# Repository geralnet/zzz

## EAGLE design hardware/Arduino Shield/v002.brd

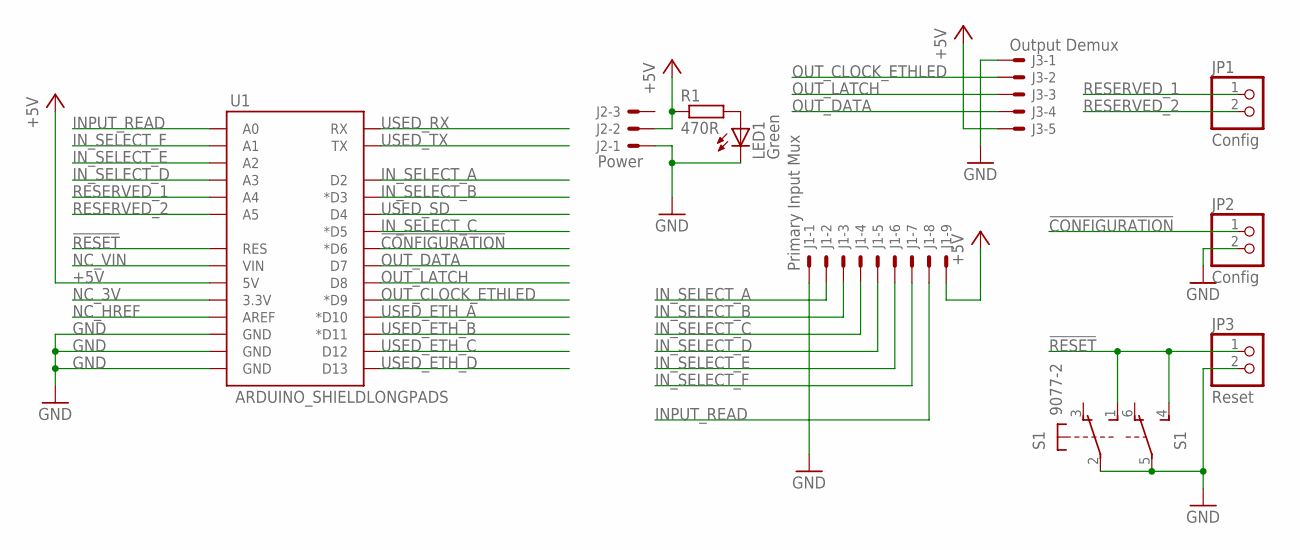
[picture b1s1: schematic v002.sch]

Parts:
J1: Primary Input Mux; 6410-09
J2: Power; 6410-03
J3: Output Demux; 6410-05
JP1, JP2: Config; 1X02
JP3: Reset; 1X02
LED1: Green; LED3MM
R1: 470R; 0204/7
S1: 9077-2
U1: ARDUINO_SHIELDLONGPADS; DUEMILANOVE_SHIELD_LONGPADS

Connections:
!CONFIGURATION: JP2.1, U1.D6 (*D6)
!RESET: JP3.1, S1.1 (S), S1.4 (S), U1.RES
+5V: J1.9, J2.2, J3.5, R1.1, U1.5V
GND: J1.1, J2.1, J3.1, JP2.2, JP3.2, LED1.K (C), S1.2, S1.5, U1.GND@0 (GND), U1.GND@1 (GND), U1.GND@2 (GND)
INPUT_READ: J1.8, U1.A0
IN_SELECT_A: J1.2, U1.D2
IN_SELECT_B: J1.3, U1.D3 (*D3)
IN_SELECT_C: J1.4, U1.D5 (*D5)
IN_SELECT_D: J1.5, U1.A3
IN_SELECT_E: J1.6, U1.A2
IN_SELECT_F: J1.7, U1.A1
unnamed: LED1.A, R1.2
NC_3V: U1.3.3V
NC_HREF: U1.AREF
NC_VIN: U1.VIN
OUT_CLOCK_ETHLED: J3.2, U1.D9 (*D9)
OUT_DATA: J3.4, U1.D7
OUT_LATCH: J3.3, U1.D8
RESERVED_1: JP1.1, U1.A4
RESERVED_2: JP1.2, U1.A5
USED_ETH_A: U1.D10 (*D10)
USED_ETH_B: U1.D11 (*D11)
USED_ETH_C: U1.D12
USED_ETH_D: U1.D13
USED_RX: U1.RX
USED_SD: U1.D4
USED_TX: U1.TX

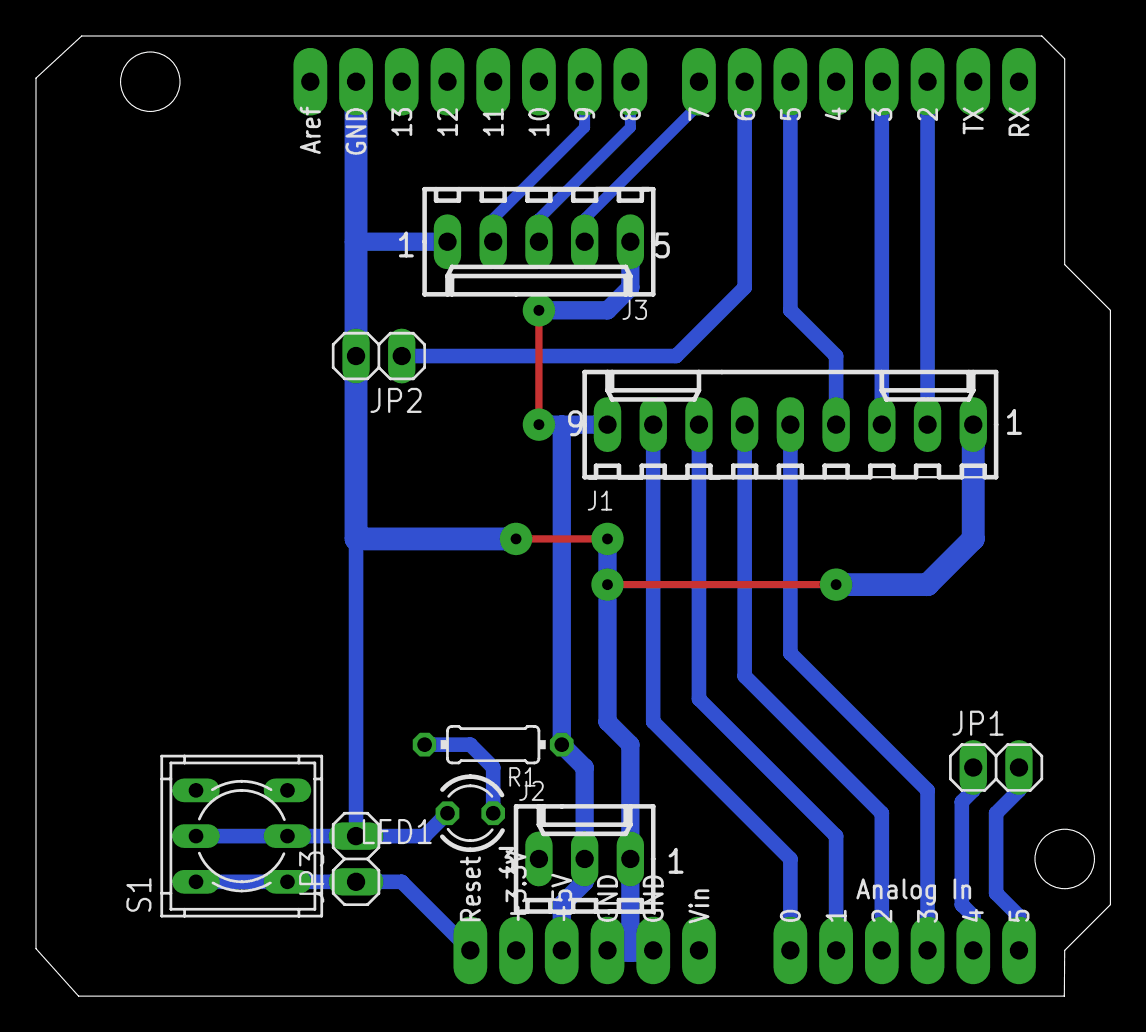
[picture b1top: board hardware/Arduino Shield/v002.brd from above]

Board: 2 copper layers, 59.7 x 53.3 mm, 10 parts (0 on the bottom side), 17 nets.

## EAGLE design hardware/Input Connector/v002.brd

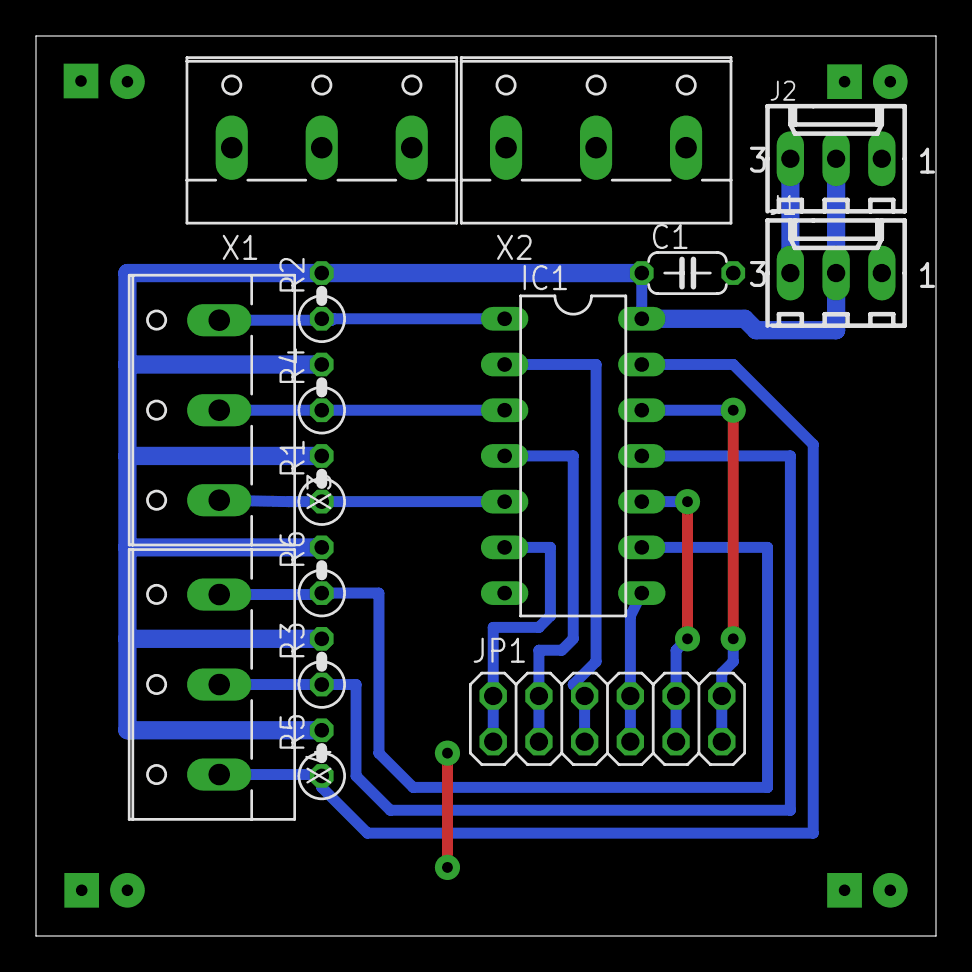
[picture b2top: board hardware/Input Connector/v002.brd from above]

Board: 2 copper layers, 50.0 x 50.0 mm, 16 parts (0 on the bottom side), 15 nets.

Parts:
C1: 0.1uF; C050-024X044
IC1: 7404; DIL14
J1: Pwr-1; 6410-03
J2: Pwr-2; 6410-03
JP1: Output; 2X06
PCB1: ZZZ_MODULE05X05; ZZZ_MODULE_05X05
R1, R2, R3, R4, R5, R6: 10K; 0207/2V
X1, X2: GND; W237-103
X3, X4: W237-103

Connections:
+5V: C1.1, IC1.14, J1.2, J2.2, R1.2, R2.2, R3.2, R4.2, R5.2, R6.2
+12V: J1.3, J2.3
GND: C1.2, IC1.7, J1.1, J2.1, PCB1.GND@1, PCB1.GND@2, PCB1.GND@3, PCB1.GND@4, PCB1.GND@5, PCB1.GND@6, PCB1.GND@7, PCB1.GND@8, X1.1, X1.2, X1.3, X2.1, X2.2, X2.3
unnamed: IC1.2, JP1.5, JP1.6
unnamed: IC1.1, R2.1, X3.3
unnamed: IC1.6, JP1.1, JP1.2
unnamed: IC1.5, R1.1, X3.1
unnamed: IC1.11, R3.1, X4.2
unnamed: IC1.10, JP1.9, JP1.10
unnamed: IC1.3, R4.1, X3.2
unnamed: IC1.12, JP1.11, JP1.12
unnamed: IC1.13, R5.1, X4.1
unnamed: IC1.8, JP1.7, JP1.8
unnamed: IC1.9, R6.1, X4.3
unnamed: IC1.4, JP1.3, JP1.4

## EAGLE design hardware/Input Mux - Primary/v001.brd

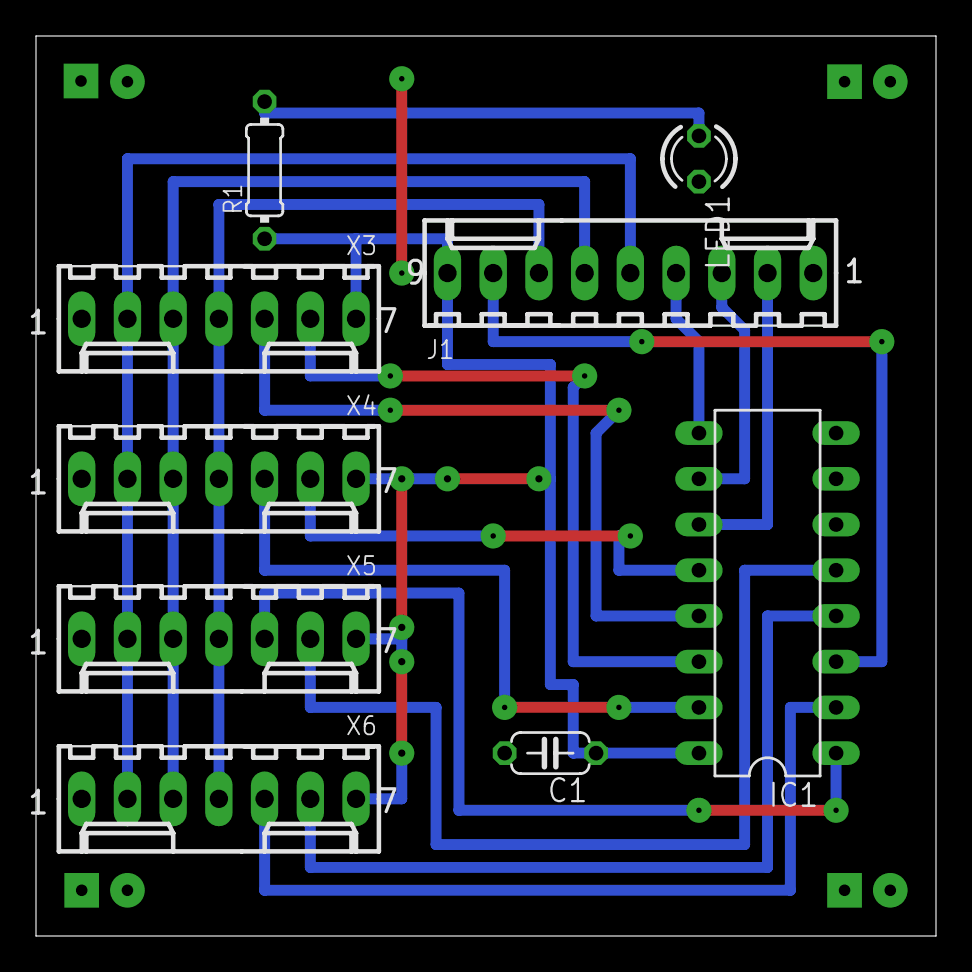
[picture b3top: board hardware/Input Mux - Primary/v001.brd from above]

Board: 2 copper layers, 50.0 x 50.0 mm, 10 parts (0 on the bottom side), 18 nets.

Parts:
C1: 0.1uF; C050-024X044
IC1: 4051N; DIL16
J1: To Arduino Shield; 6410-09
LED1: Green; LED3MM
PCB1: ZZZ_MODULE05X05; ZZZ_MODULE_05X05
R1: 470R; 0204/7
X3: Sec 12; 6410-07
X4: Sec 34; 6410-07
X5: Sec 56; 6410-07
X6: Sec 78; 6410-07

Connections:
+5V: C1.1, IC1.16, J1.9, R1.1, X3.7, X4.7, X5.7, X6.7
GND: C1.2, IC1.6, IC1.7, IC1.8, J1.1, LED1.K, PCB1.GND@1, PCB1.GND@2, PCB1.GND@3, PCB1.GND@4, PCB1.GND@5, PCB1.GND@6, PCB1.GND@7, PCB1.GND@8, X3.1, X4.1, X5.1, X6.1
INPUT_READ: IC1.3, J1.8
unnamed: LED1.A, R1.2
SECONDARY_1: IC1.13, X3.5
SECONDARY_2: IC1.14, X3.6
SECONDARY_3: IC1.15, X4.5
SECONDARY_4: IC1.12, X4.6
SECONDARY_5: IC1.1, X5.5
SECONDARY_6: IC1.5, X5.6
SECONDARY_7: IC1.2, X6.5
SECONDARY_8: IC1.4, X6.6
SELECT_A: IC1.11, J1.2
SELECT_B: IC1.10, J1.3
SELECT_C: IC1.9, J1.4
SELECT_D: J1.5, X3.2, X4.2, X5.2, X6.2
SELECT_E: J1.6, X3.3, X4.3, X5.3, X6.3
SELECT_F: J1.7, X3.4, X4.4, X5.4, X6.4

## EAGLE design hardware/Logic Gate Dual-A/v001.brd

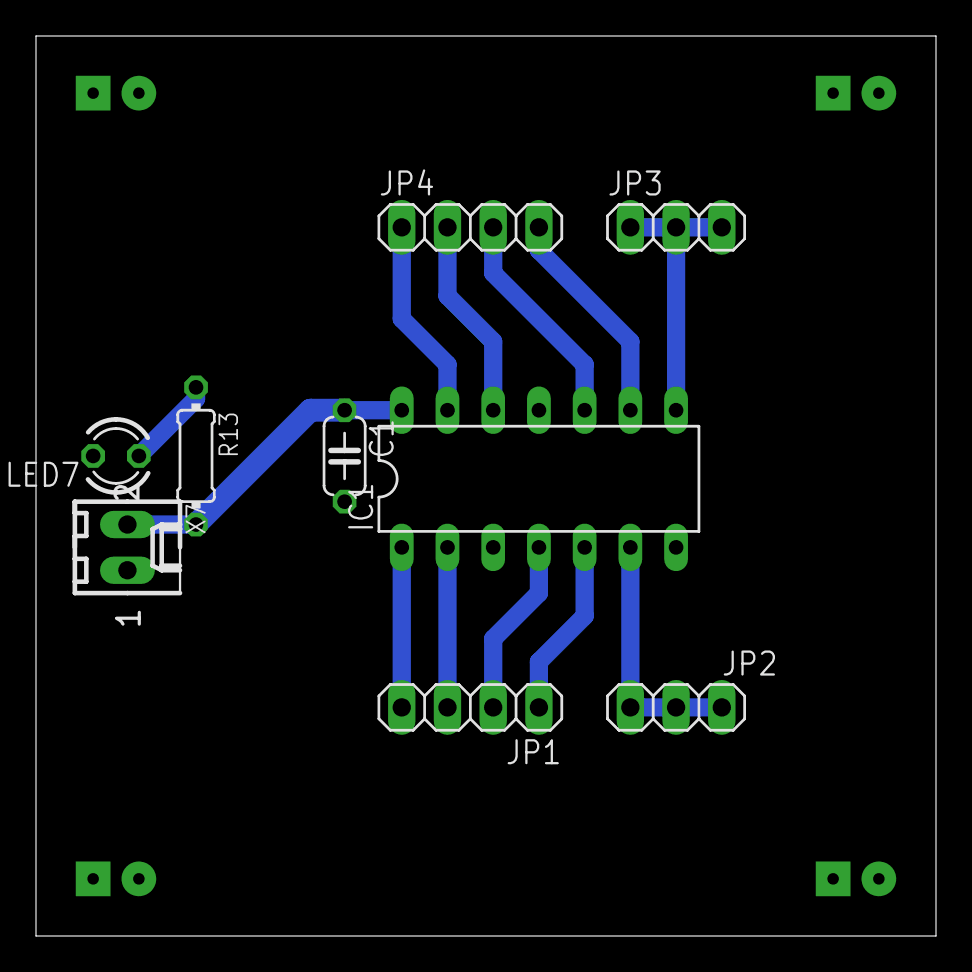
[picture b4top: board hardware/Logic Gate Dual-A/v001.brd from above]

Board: 2 copper layers, 50.0 x 50.0 mm, 10 parts (0 on the bottom side), 13 nets.

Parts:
C1: 0.1uF; C050-024X044
IC1: Like 7421; DIL14
JP1, JP4: Input; 1X04
JP2, JP3: Output; 1X03
LED7: Green; LED3MM
PCB1: PCB05X05; PCB_05X05
R13: 470R; 0204/7
X7: Power; 6410-02

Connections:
+5V: C1.1, IC1.14, R13.2, X7.2
GND: C1.2, IC1.7, LED7.K, PCB1.GND@1, PCB1.GND@2, PCB1.GND@3, PCB1.GND@4, PCB1.GND@5, PCB1.GND@6, PCB1.GND@7, PCB1.GND@8, X7.1
unnamed: IC1.1, JP1.4
unnamed: IC1.2, JP1.3
unnamed: IC1.6, JP2.1, JP2.2, JP2.3
unnamed: IC1.4, JP1.2
unnamed: LED7.A, R13.1
unnamed: IC1.5, JP1.1
unnamed: IC1.8, JP3.1, JP3.2, JP3.3
unnamed: IC1.9, JP4.4
unnamed: IC1.10, JP4.3
unnamed: IC1.12, JP4.2
unnamed: IC1.13, JP4.1

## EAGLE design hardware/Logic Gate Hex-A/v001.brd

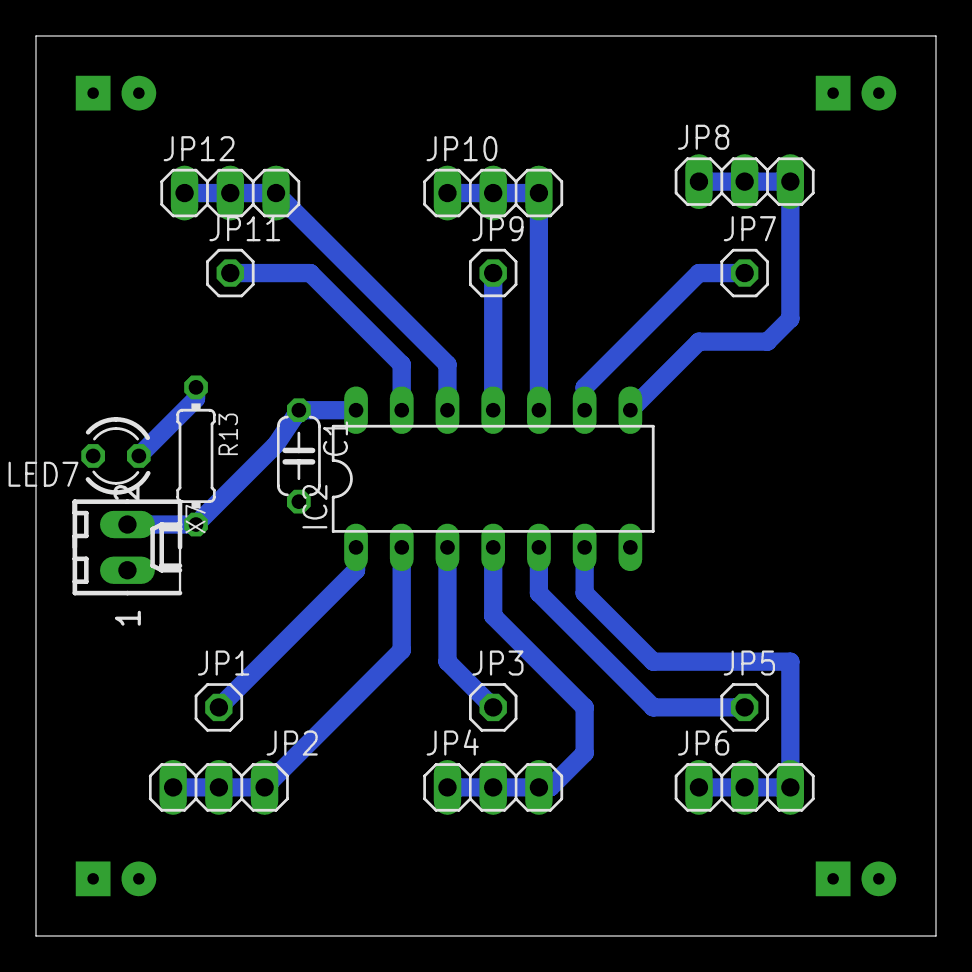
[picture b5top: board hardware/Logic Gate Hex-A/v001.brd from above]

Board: 2 copper layers, 50.0 x 50.0 mm, 18 parts (0 on the bottom side), 15 nets.

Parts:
C1: 0.1uF; C050-024X044
IC2: Like 7404; DIL14
JP1, JP3, JP5, JP7, JP9, JP11: 1X01
JP2, JP4, JP6, JP8, JP10, JP12: Output; 1X03
LED7: Green; LED3MM
PCB1: PCB05X05; PCB_05X05
R13: 470R; 0204/7
X7: Power; 6410-02

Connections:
+5V: C1.1, IC2.14, R13.2, X7.2
GND: C1.2, IC2.7, LED7.K, PCB1.GND@1, PCB1.GND@2, PCB1.GND@3, PCB1.GND@4, PCB1.GND@5, PCB1.GND@6, PCB1.GND@7, PCB1.GND@8, X7.1
JP12: IC2.12, JP12.1, JP12.2, JP12.3
unnamed: IC2.1, JP1.1
unnamed: IC2.2, JP2.1, JP2.2, JP2.3
unnamed: LED7.A, R13.1
unnamed: IC2.3, JP3.1
unnamed: IC2.4, JP4.1, JP4.2, JP4.3
unnamed: IC2.5, JP5.1
unnamed: IC2.6, JP6.1, JP6.2, JP6.3
unnamed: IC2.9, JP7.1
unnamed: IC2.8, JP8.1, JP8.2, JP8.3
unnamed: IC2.11, JP9.1
unnamed: IC2.10, JP10.1, JP10.2, JP10.3
unnamed: IC2.13, JP11.1

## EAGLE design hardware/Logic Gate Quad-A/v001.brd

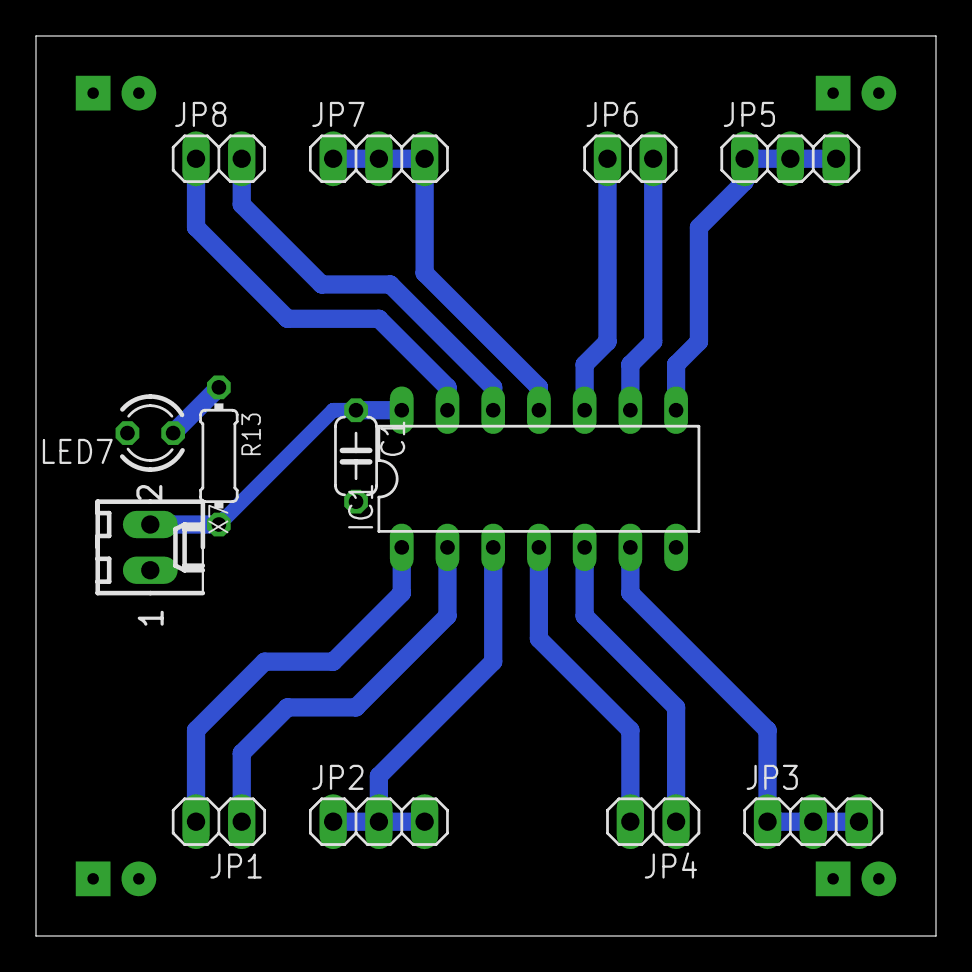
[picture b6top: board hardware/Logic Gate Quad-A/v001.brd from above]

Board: 2 copper layers, 50.0 x 50.0 mm, 14 parts (0 on the bottom side), 15 nets.

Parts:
C1: 0.1uF; C050-024X044
IC1: Like 7408; DIL14
JP1, JP4, JP6, JP8: 1X02
JP2, JP3, JP5, JP7: Output; 1X03
LED7: Green; LED3MM
PCB1: PCB05X05; PCB_05X05
R13: 470R; 0204/7
X7: Power; 6410-02

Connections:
+5V: C1.1, IC1.14, R13.2, X7.2
GND: C1.2, IC1.7, LED7.K, PCB1.GND@1, PCB1.GND@2, PCB1.GND@3, PCB1.GND@4, PCB1.GND@5, PCB1.GND@6, PCB1.GND@7, PCB1.GND@8, X7.1
unnamed: IC1.1, JP1.2
unnamed: IC1.2, JP1.1
unnamed: IC1.3, JP2.1, JP2.2, JP2.3
unnamed: IC1.4, JP4.2
unnamed: LED7.A, R13.1
unnamed: IC1.5, JP4.1
unnamed: IC1.6, JP3.1, JP3.2, JP3.3
unnamed: IC1.9, JP6.2
unnamed: IC1.10, JP6.1
unnamed: IC1.8, JP5.1, JP5.2, JP5.3
unnamed: IC1.12, JP8.2
unnamed: IC1.13, JP8.1
unnamed: IC1.11, JP7.1, JP7.2, JP7.3

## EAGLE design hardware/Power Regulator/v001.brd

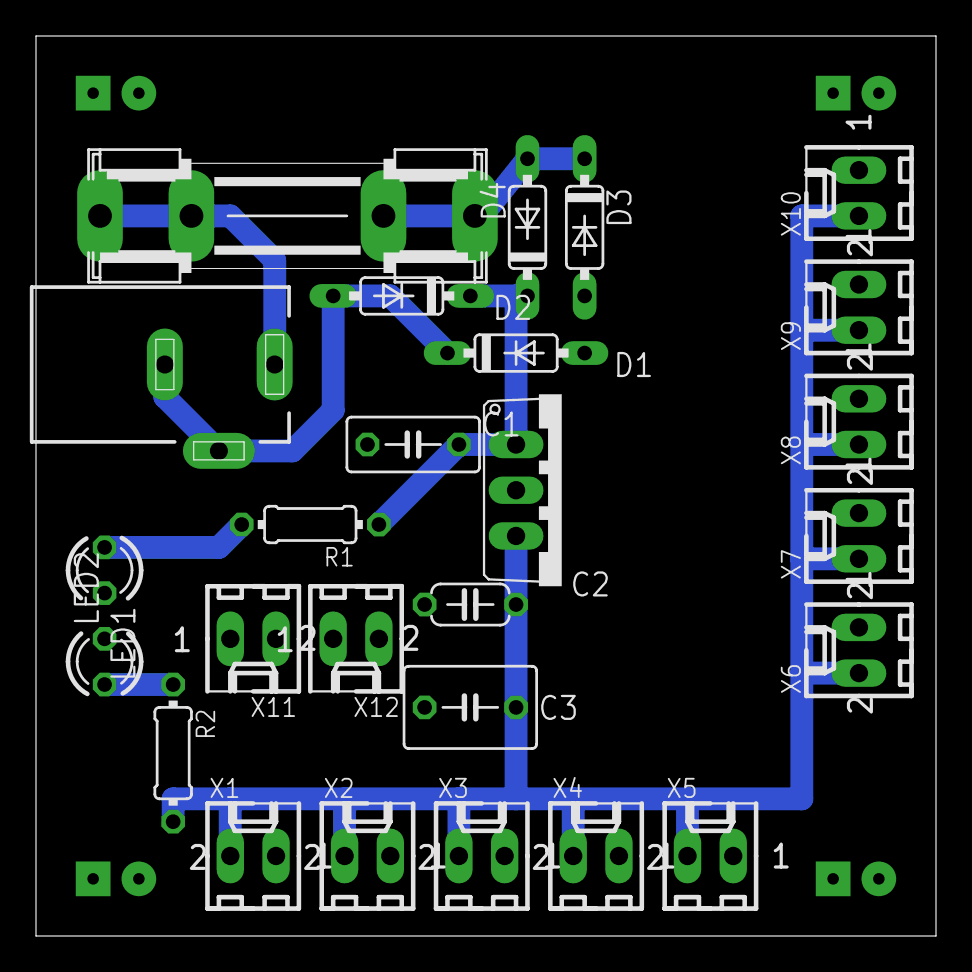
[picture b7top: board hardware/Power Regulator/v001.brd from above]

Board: 2 copper layers, 50.0 x 50.0 mm, 27 parts (0 on the bottom side), 8 nets.

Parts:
C1: 0.33uF; C050-030X075
C2: 0.1uF; C050-024X044
C3: 1uF; C050-045X075
D1, D2, D3, D4: 1N4004; DO35-7
F1: 1A; SHK20L
IC1: 7805TV; TO220V
J1: 9VDC; DCJ0202
LED1, LED2: GREEN; LED3MM
PCB1: PCB05X05; PCB_05X05
R1, R2: 470R; 0204/7
X1: Out-A; 6410-02
X2: Out-B; 6410-02
X3: Out-C; 6410-02
X4: Out-D; 6410-02
X5: Out-E; 6410-02
X6: Out-F; 6410-02
X7: Out-G; 6410-02
X8: Out-H; 6410-02
X9: Out-I; 6410-02
X10: Out-J; 6410-02
X11, X12: Cross; 6410-02

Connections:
+5V: C2.1, C3.1, IC1.3, R2.2, X1.2, X2.2, X3.2, X4.2, X5.2, X6.2, X7.2, X8.2, X9.2, X10.2
GND: C1.2, C2.2, C3.2, D1.A, D3.A, IC1.2, LED1.K, LED2.K, PCB1.GND@1, PCB1.GND@2, PCB1.GND@3, PCB1.GND@4, PCB1.GND@5, PCB1.GND@6, PCB1.GND@7, PCB1.GND@8, X1.1, X2.1, X3.1, X4.1, X5.1, X6.1, X7.1, X8.1, X9.1, X10.1, X11.1, X12.1
unnamed: C1.1, D2.C, D4.C, IC1.1, R1.1
unnamed: LED1.A, R1.2
unnamed: F1.1A, J1.1
unnamed: LED2.A, R2.1
unnamed: D1.C, D2.A, J1.2, J1.3
unnamed: D3.C, D4.A, F1.2A

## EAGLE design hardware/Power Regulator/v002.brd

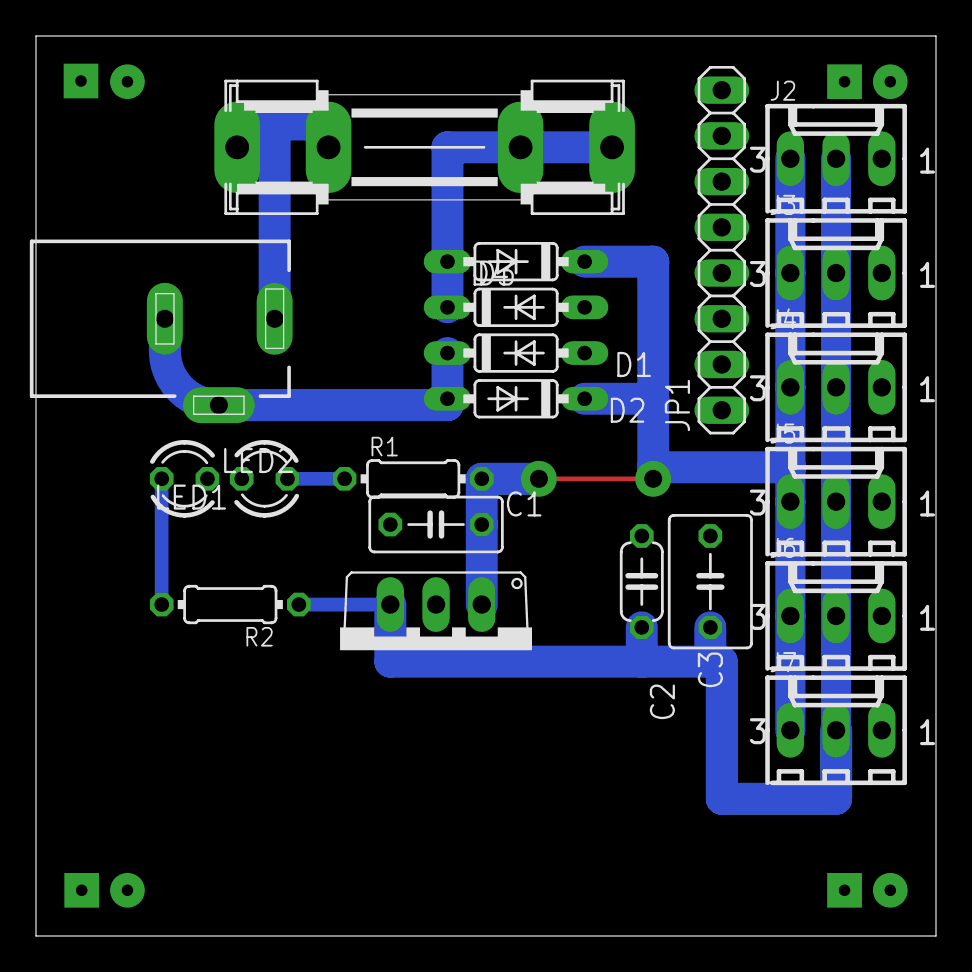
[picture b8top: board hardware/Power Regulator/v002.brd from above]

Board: 2 copper layers, 50.0 x 50.0 mm, 22 parts (0 on the bottom side), 8 nets.

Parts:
C1: 0.33uF; C050-030X075
C2: 0.1uF; C050-024X044
C3: 1uF; C050-045X075
D1, D2, D3, D4: 1N4004; DO35-7
F1: 3A; SHK20L
IC1: 7805TV; TO220V
J1: 12VDC; DCJ0202
J2: Out-1; 6410-03
J3: Out-2; 6410-03
J4: Out-3; 6410-03
J5: Out-4; 6410-03
J6: Out-5; 6410-03
J7: Out-6; 6410-03
JP1: GND; 1X08
LED1, LED2: GREEN; LED3MM
PCB1: ZZZ_MODULE05X05; ZZZ_MODULE_05X05
R1, R2: 470R; 0204/7

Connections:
+5V: C2.1, C3.1, IC1.3, J2.2, J3.2, J4.2, J5.2, J6.2, J7.2, R2.1
+12V: C1.1, D2.C, D4.C, IC1.1, J2.3, J3.3, J4.3, J5.3, J6.3, J7.3, R1.2
GND: C1.2, C2.2, C3.2, D1.A, D3.A, IC1.2, J2.1, J3.1, J4.1, J5.1, J6.1, J7.1, JP1.1, JP1.2, JP1.3, JP1.4, JP1.5, JP1.6, JP1.7, JP1.8, LED1.K, LED2.K, PCB1.GND@1, PCB1.GND@2, PCB1.GND@3, PCB1.GND@4, PCB1.GND@5, PCB1.GND@6, PCB1.GND@7, PCB1.GND@8
unnamed: LED1.A, R1.1
unnamed: LED2.A, R2.2
unnamed: F1.1A, J1.1
unnamed: D1.C, D2.A, J1.2, J1.3
unnamed: D3.C, D4.A, F1.2A

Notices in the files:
parts and their libraries:
SparkFun-Boards: Licensing: CC v3.0 Share-Alike You are welcome to use this library for commercial purposes.
